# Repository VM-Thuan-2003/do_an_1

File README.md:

# PROJECT - ELECTRONIC - 1

> Name project: He thong giam sat nhiet do ho ca va cho ca an tu dong

## 2 MEMBER
* Vo Minh Thuan - 21161366
* Le Quang Thuong - 21161366

>Contact: 0355524273

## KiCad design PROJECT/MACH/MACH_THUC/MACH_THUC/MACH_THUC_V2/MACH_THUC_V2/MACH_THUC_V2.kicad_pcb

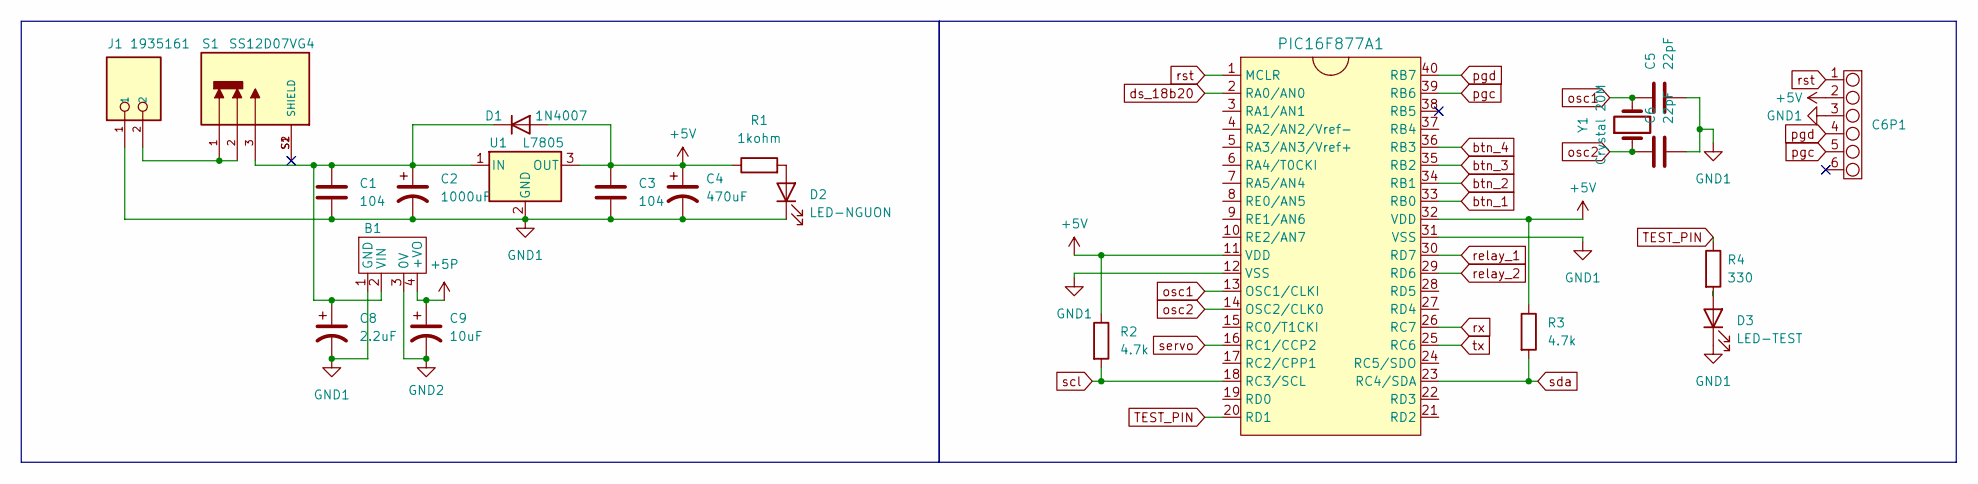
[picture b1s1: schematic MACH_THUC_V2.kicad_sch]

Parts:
B1: B1205S-1WR3_12_5V
C1, C3: 104; CAP_104
C2: 1000uF; CAP_1000uF
C4: 470uF; CAP_470uF
C5, C6: 22pF; CAP_104
C6P1: CONNECT_6PIN
C8: 2.2uF; CAP_2.2uF
C9: 10uF; CAP_10uF
D1: 1N4007
D2: LED-NGUON; LED_5MM
D3: LED-TEST; LED_5MM
J1: 1935161; PHOENIX_1935161; PARTREV 14.12.2022
PIC16F877A1: PIC_16F877A
R1: 1kohm; RES_DEFAULT
R2, R3: 4.7k; RES_DEFAULT
R4: 330; RES_DEFAULT
S1: SS12D07VG4; SW_SS12D07VG4; PARTREV 1
U1: L7805; TO255P1020X450X2000-3
Y1: Crystal 20M; crytal_20M

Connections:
pgd: C6P1.4, PIC16F877A1.40 (RB7)
+5P: B1.4 (+VO), C9.1
+5V: C3.1, C4.1, C6P1.2, D1.2 (A), PIC16F877A1.11 (VDD), PIC16F877A1.32 (VDD), R1.1, R2.1, R3.1, U1.3 (OUT)
GND1: B1.1 (GND), C1.2, C2.2, C3.2, C4.2, C5.2, C6.2, C6P1.3, C8.2, D2.1 (K), D3.1 (K), J1.1, PIC16F877A1.12 (VSS), PIC16F877A1.31 (VSS), U1.2 (GND)
GND2: B1.3 (0V), C9.2
unnamed: B1.2 (VIN), C1.1, C2.1, C8.1, D1.1 (K), S1.3, U1.1 (IN)
unnamed: D2.2 (A), R1.2
unnamed: D3.2 (A), R4.2
unnamed: J1.2, S1.1, S1.2
TEST_PIN: PIC16F877A1.20 (RD1), R4.1
btn_1: PIC16F877A1.33 (RB0)
btn_2: PIC16F877A1.34 (RB1)
btn_3: PIC16F877A1.35 (RB2)
btn_4: PIC16F877A1.36 (RB3)
ds_18b20: PIC16F877A1.2 (RA0/AN0)
osc1: C5.1, PIC16F877A1.13 (OSC1/CLKI), Y1.2
osc2: C6.1, PIC16F877A1.14 (OSC2/CLK0), Y1.1
pgc: C6P1.5, PIC16F877A1.39 (RB6)
relay_1: PIC16F877A1.30 (RD7)
relay_2: PIC16F877A1.29 (RD6)
rst: C6P1.1, PIC16F877A1.1 (MCLR)
rx: PIC16F877A1.26 (RC7)
scl: PIC16F877A1.18 (RC3/SCL), R2.2
sda: PIC16F877A1.23 (RC4/SDA), R3.2
servo: PIC16F877A1.16 (RC1/CCP2)
tx: PIC16F877A1.25 (RC6)

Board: 2 copper layers, 22 parts (0 on the bottom side), 16 nets, no tracks yet.

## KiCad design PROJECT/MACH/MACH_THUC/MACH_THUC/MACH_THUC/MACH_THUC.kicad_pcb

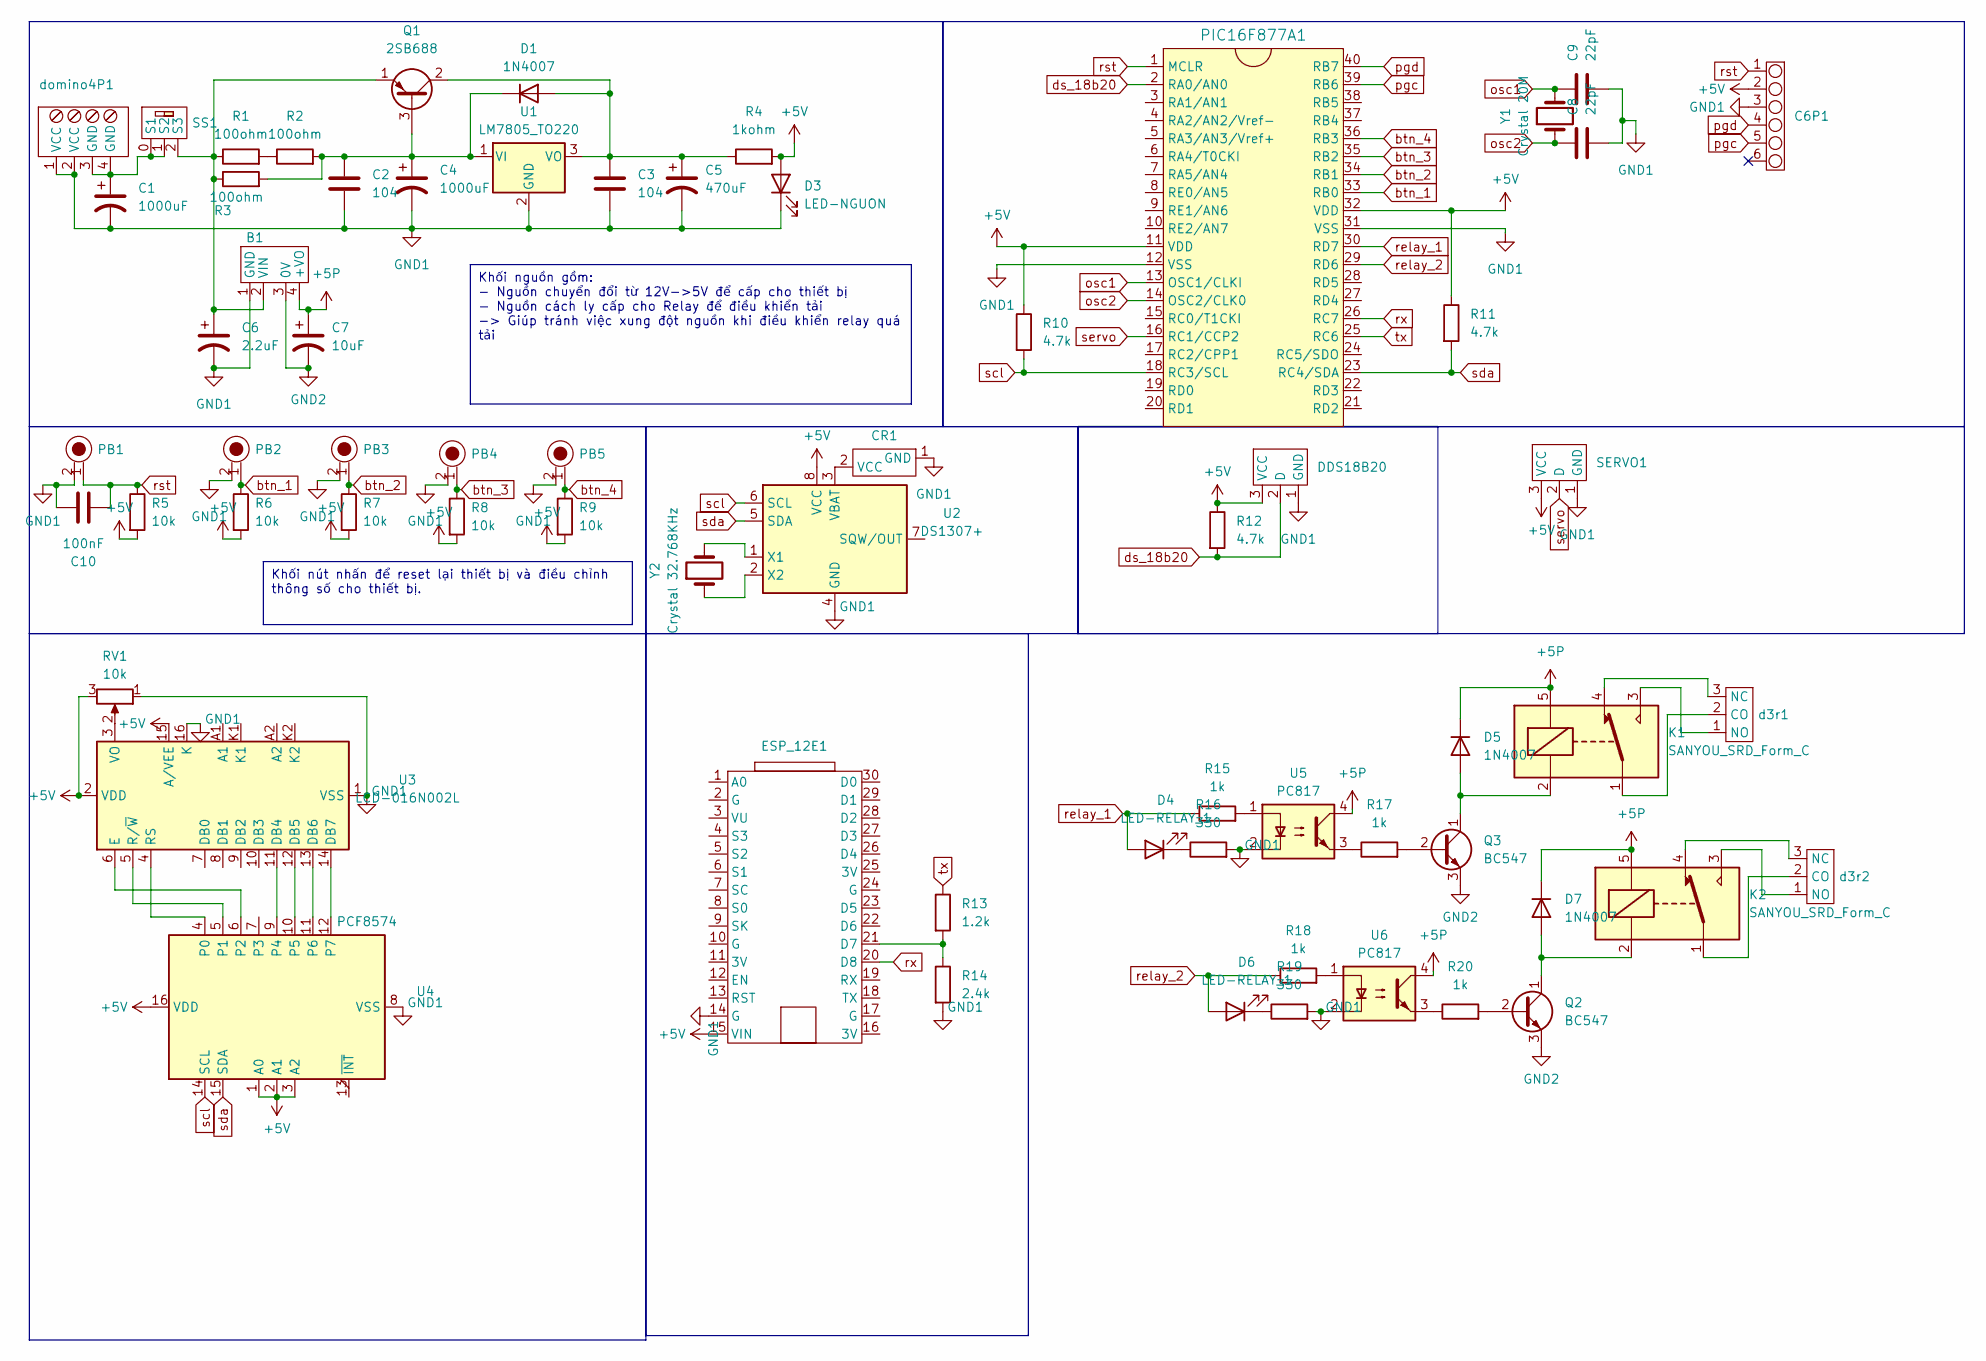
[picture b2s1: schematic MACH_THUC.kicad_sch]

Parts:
B1: B1205S-1WR3_12_5V
C1, C4: 1000uF; CAP_1000uF
C2, C3: 104; CAP_104
C5: 470uF; CAP_470uF
C6: 2.2uF; CAP_2.2uF
C6P1: CONNECT_6PIN
C7: 10uF; CAP_10uF
C8, C9: 22pF; CAP_104
C10: 100nF; CAP_104
CR1: cr2032
D1, D5, D7: 1N4007
D3: LED-NGUON; LED_5MM
D4, D6: LED-RELAY_1; LED_5MM
DDS18B20: DOMINO_3
ESP_12E1: ESP8266_12E
K1, K2: SANYOU_SRD_Form_C; Relay_SPDT_SANYOU_SRD_Series_Form_C
PB1, PB2, PB3, PB4, PB5: push_button
PIC16F877A1: PIC_16F877A
Q1: 2SB688; TO-218-3_Vertical
Q2, Q3: BC547; TO-92_Inline
R1, R2, R3: 100ohm; RES_1ohm_1w
R4: 1kohm; RES_DEFAULT
R5, R6, R7, R8, R9: 10k; RES_DEFAULT
R10, R11, R12: 4.7k; RES_DEFAULT
R13: 1.2k; RES_DEFAULT
R14: 2.4k; RES_DEFAULT
R15, R17, R18, R20: 1k; RES_DEFAULT
R16, R19: 330; RES_DEFAULT
RV1: 10k; RM065-103
SERVO1: DOMINO_3
SS1: SWITCH_SLIDER
U1: LM7805_TO220; TO-220-3_Vertical
U2: DS1307+; DIP-8_W7.62mm
U3: LCD-016N002L
U4: PCF8574; SOIC127P1032X265-16N
U5, U6: PC817; DIP-4_W7.62mm
Y1: Crystal 20M; crytal_20M
Y2: Crystal 32.768KHz; crytal_32.768KHz
d3r1, d3r2: DOMINO_3_5mm
domino4P1: DOMINO_4_5mm

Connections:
pgd: C6P1.4, PIC16F877A1.40 (RB7)
+5P: B1.4 (+VO), C7.1, D5.1 (K), D7.1 (K), K1.5, K2.5, U5.4, U6.4
+5V: C6P1.2, D3.2 (A), DDS18B20.3 (VCC), ESP_12E1.15 (VIN), PIC16F877A1.11 (VDD), PIC16F877A1.32 (VDD), R4.2, R5.2, R6.2, R7.2, R8.2, R9.2, R10.1, R11.1, R12.1, RV1.3, SERVO1.3 (VCC), U2.8 (VCC), U3.2 (VDD), U3.15 (A/VEE), U4.1 (A0), U4.2 (A1), U4.3 (A2), U4.16 (VDD)
GND1: B1.1 (GND), C1.2, C2.2, C3.2, C4.2, C5.2, C6.2, C6P1.3, C8.2, C9.2, C10.2, CR1.1 (GND), D3.1 (K), DDS18B20.1 (GND), ESP_12E1.14 (G), PB1.2, PB2.2, PB3.2, PB4.2, PB5.2, PIC16F877A1.12 (VSS), PIC16F877A1.31 (VSS), R14.2, R16.2, R19.2, RV1.1, SERVO1.1 (GND), U1.2 (GND), U2.4 (GND), U3.1 (VSS), U3.16 (K), U4.8 (VSS), U5.2, U6.2, domino4P1.1 (VCC), domino4P1.2 (VCC)
GND2: B1.3 (0V), C7.2, Q2.3 (E), Q3.3 (E)
unnamed: B1.2 (VIN), C6.1, Q1.1 (E), R1.1, R3.1, SS1.2 (S3)
unnamed: CR1.2 (VCC), U2.3 (VBAT)
unnamed: C3.1, C5.1, D1.2 (A), Q1.2 (C), R4.1, U1.3 (VO)
unnamed: C2.1, C4.1, D1.1 (K), Q1.3 (B), R2.2, R3.2, U1.1 (VI)
unnamed: D4.1 (K), R16.1
unnamed: D5.2 (A), K1.2, Q3.1 (C)
unnamed: D6.1 (K), R19.1
unnamed: D7.2 (A), K2.2, Q2.1 (C)
unnamed: ESP_12E1.21 (D7), R13.2, R14.1
unnamed: Q2.2 (B), R20.2
unnamed: Q3.2 (B), R17.2
unnamed: R1.2, R2.1
unnamed: R15.2, U5.1
unnamed: R17.1, U5.3
unnamed: R18.2, U6.1
unnamed: R20.1, U6.3
unnamed: C1.1, SS1.0 (S1), SS1.1 (S2), domino4P1.3 (GND), domino4P1.4 (GND)
unnamed: U2.1 (X1), Y2.2
unnamed: U2.2 (X2), Y2.1
unnamed: U3.11 (DB4), U4.9 (P4)
unnamed: U3.12 (DB5), U4.10 (P5)
unnamed: U3.13 (DB6), U4.11 (P6)
unnamed: U3.14 (DB7), U4.12 (P7)
unnamed: U3.6 (E), U4.6 (P2)
unnamed: U3.4 (RS), U4.4 (P0)
unnamed: U3.5 (R/~W), U4.5 (P1)
unnamed: RV1.2, U3.3 (VO)
unnamed: K1.1, d3r1.2 (CO)
unnamed: K1.4, d3r1.3 (NC)
unnamed: K1.3, d3r1.1 (NO)
unnamed: K2.1, d3r2.2 (CO)
unnamed: K2.4, d3r2.3 (NC)
unnamed: K2.3, d3r2.1 (NO)
btn_1: PB2.1, PIC16F877A1.33 (RB0), R6.1
btn_2: PB3.1, PIC16F877A1.34 (RB1), R7.1
btn_3: PB4.1, PIC16F877A1.35 (RB2), R8.1
btn_4: PB5.1, PIC16F877A1.36 (RB3), R9.1
ds_18b20: DDS18B20.2 (D), PIC16F877A1.2 (RA0/AN0), R12.2
osc1: C9.1, PIC16F877A1.13 (OSC1/CLKI), Y1.2
osc2: C8.1, PIC16F877A1.14 (OSC2/CLK0), Y1.1
pgc: C6P1.5, PIC16F877A1.39 (RB6)
relay_1: D4.2 (A), PIC16F877A1.30 (RD7), R15.1
relay_2: D6.2 (A), PIC16F877A1.29 (RD6), R18.1
rst: C6P1.1, C10.1, PB1.1, PIC16F877A1.1 (MCLR), R5.1
rx: ESP_12E1.20 (D8), PIC16F877A1.26 (RC7)
scl: PIC16F877A1.18 (RC3/SCL), R10.2, U2.6 (SCL), U4.14 (SCL)
sda: PIC16F877A1.23 (RC4/SDA), R11.2, U2.5 (SDA), U4.15 (SDA)
servo: PIC16F877A1.16 (RC1/CCP2), SERVO1.2 (D)
tx: PIC16F877A1.25 (RC6), R13.1

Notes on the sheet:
Khối nguồn gồm: - Nguồn chuyển đổi từ 12V->5V để cấp cho thiết bị - Nguồn cách ly cấp cho Relay để điều khiển tải -> Giúp tránh việc xung đột nguồn khi điều khiển relay quá tải
Khối nút nhấn để reset lại thiết bị và điều chỉnh thông số cho thiết bị.

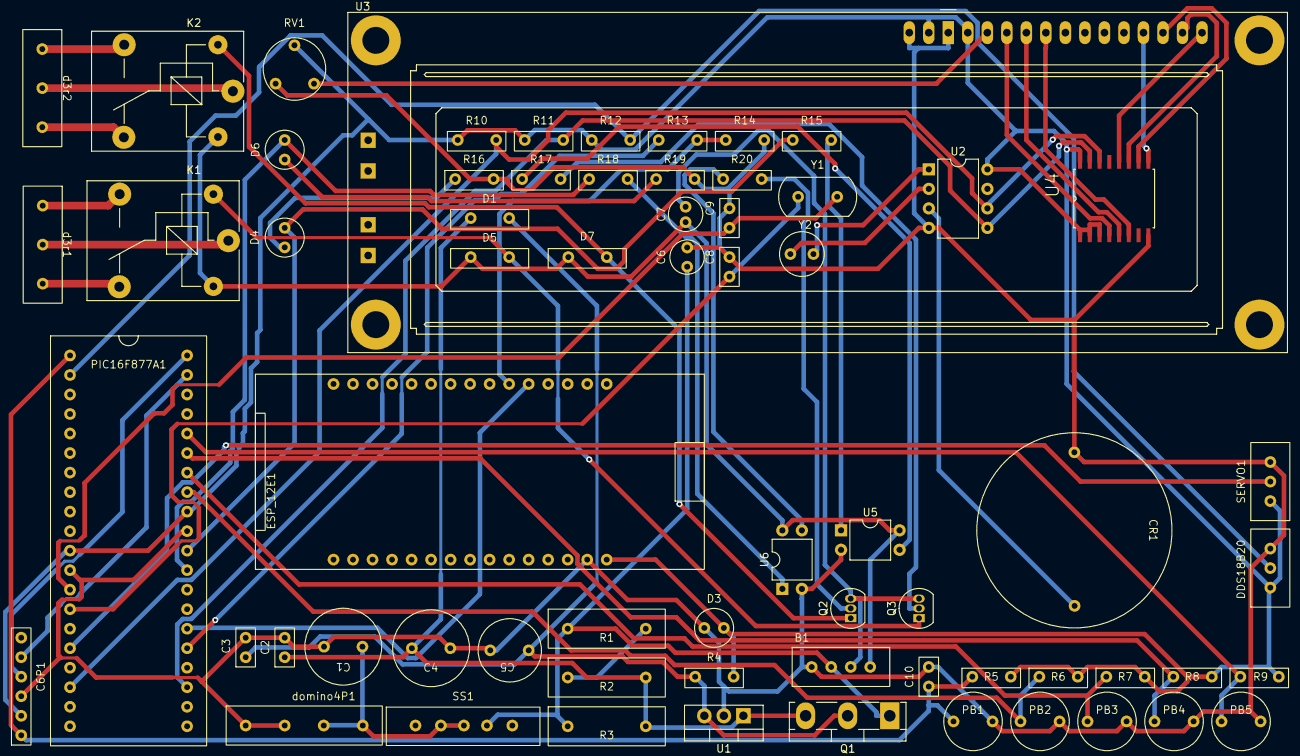
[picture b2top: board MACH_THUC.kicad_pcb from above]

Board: 2 copper layers, 66 parts (0 on the bottom side), 54 nets.

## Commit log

2024-03-10 dev first commit
2024-03-12 update code
2024-03-15 update code do_an_1
2024-03-19 dev fix code ds1307
2024-05-01 update code'
2024-06-01 update code final
2024-06-02 update code finall for project
2024-06-02 update code finall
2024-06-09 update final for uart esp and pic16f
2024-06-20 update for finnal code
